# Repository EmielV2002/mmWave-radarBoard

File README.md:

# mmWave-radarBoard
 
# This is project is still work-in-progress!

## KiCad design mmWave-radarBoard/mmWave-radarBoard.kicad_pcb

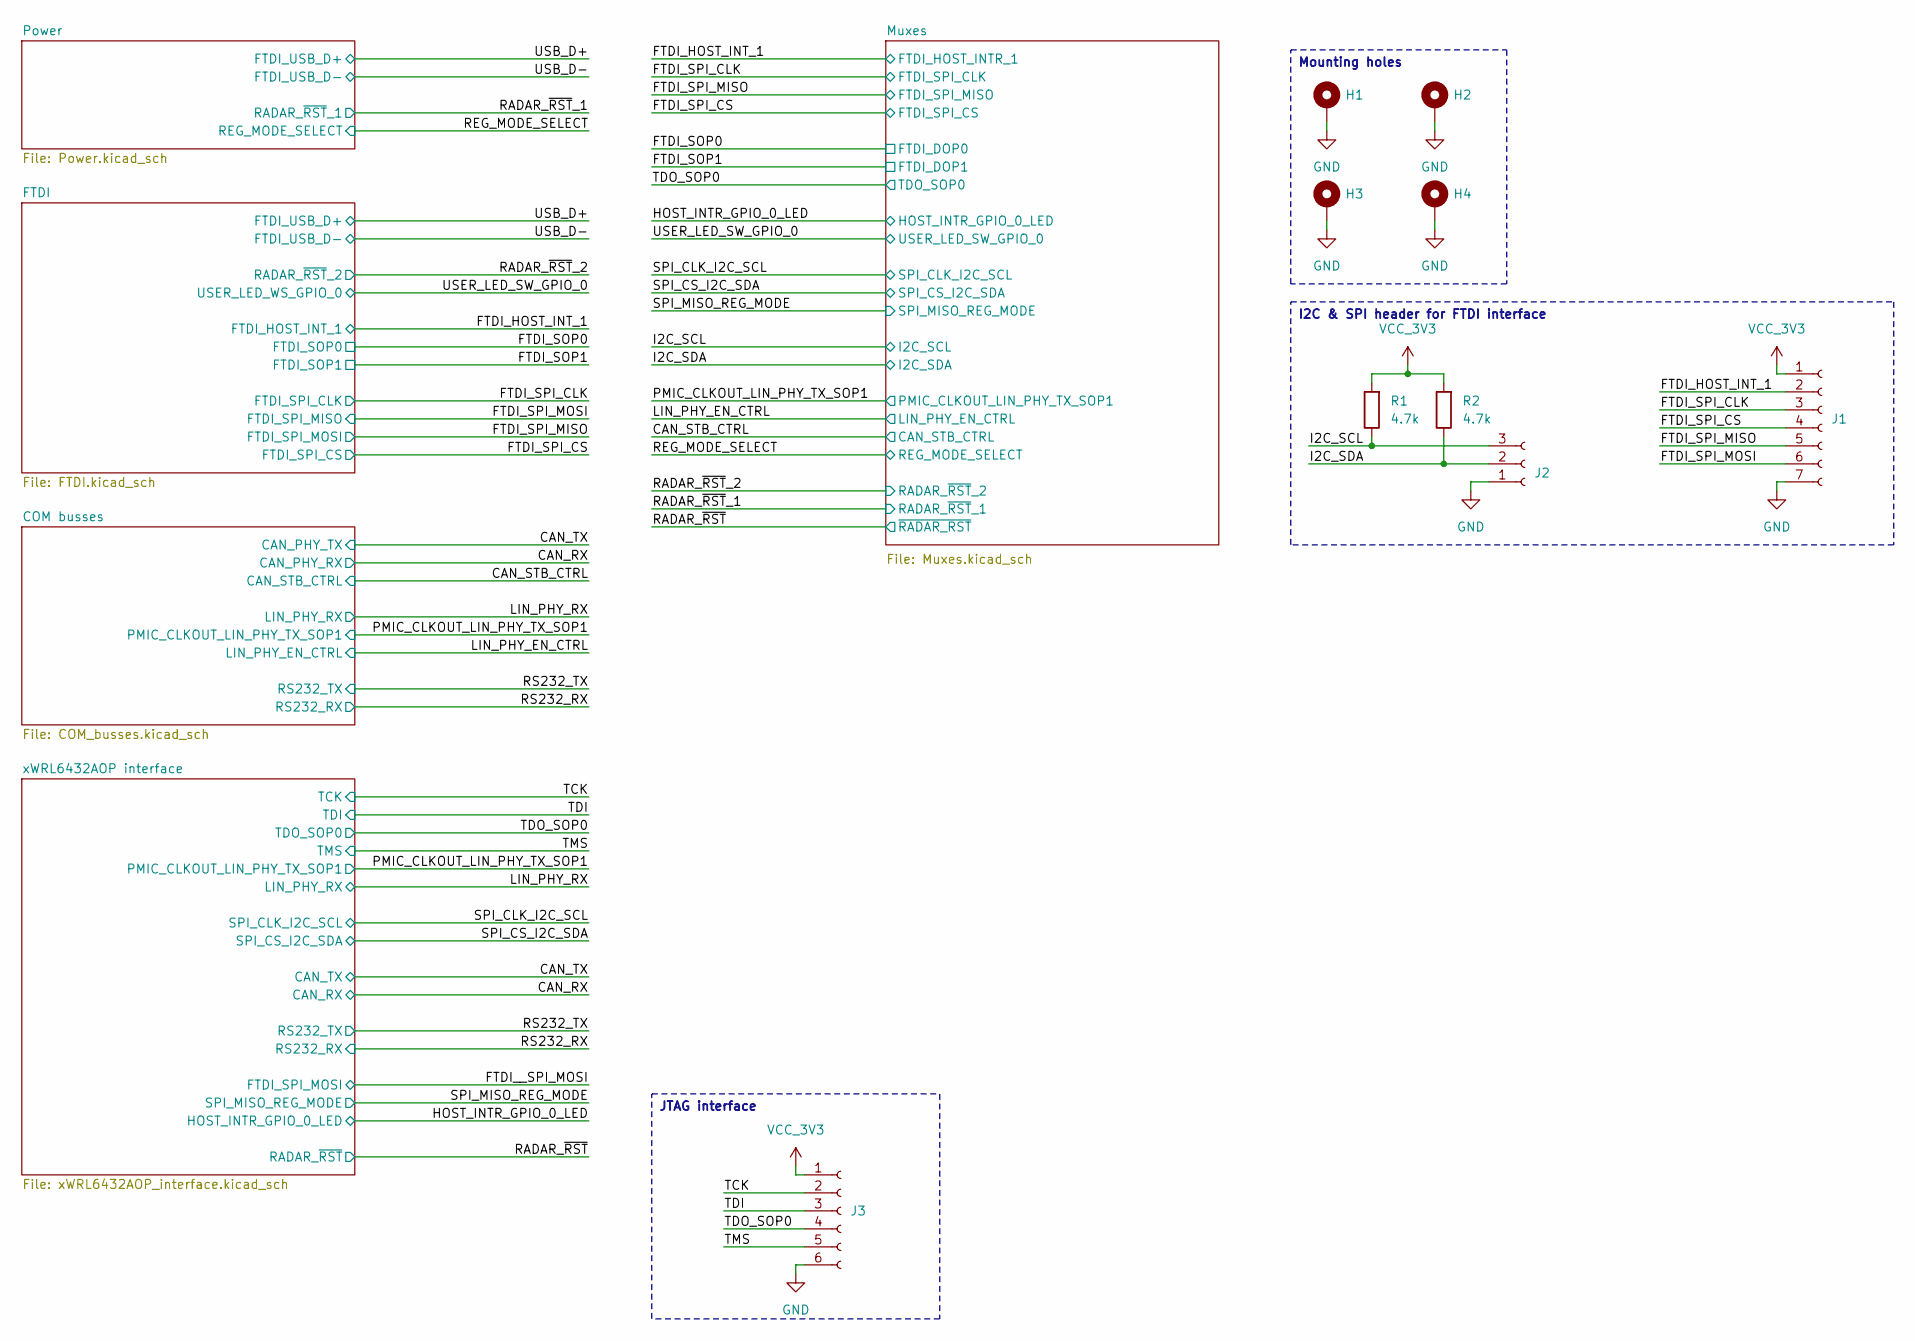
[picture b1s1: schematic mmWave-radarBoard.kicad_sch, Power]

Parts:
H1, H2, H3, H4: MountingHole; MountingHole_2.7mm_M2.5_DIN965_Pad
J1: Conn_01x07_Socket; JST_ZH_B7B-ZR_1x07_P1.50mm_Vertical
J2: Conn_01x03_Socket; JST_ZE_B03B-ZESK-D_1x03_P1.50mm_Vertical
J3: Conn_01x06_Socket; JST_ZH_B6B-ZR_1x06_P1.50mm_Vertical
R1, R2: 4.7k; R_0402_1005Metric

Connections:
/FTDI_HOST_INT_1: J1.2; also elsewhere on the board
/FTDI_SPI_CLK: J1.3; also elsewhere on the board
/FTDI_SPI_CS: J1.4; also elsewhere on the board
/FTDI_SPI_MISO: J1.5; also elsewhere on the board
/FTDI_SPI_MOSI: J1.6; also elsewhere on the board
/I2C_SCL: J2.3, R1.1; also elsewhere on the board
/I2C_SDA: J2.2, R2.1; also elsewhere on the board
/TCK: J3.2; also elsewhere on the board
/TDI: J3.3; also elsewhere on the board
/TDO_SOP0: J3.4; also elsewhere on the board
/TMS: J3.5; also elsewhere on the board
GND: H1.1, H2.1, H3.1, H4.1, J1.7, J2.1, J3.6; also elsewhere on the board
VCC_3V3: J1.1, J3.1, R1.2, R2.2; also elsewhere on the board

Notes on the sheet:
Mounting holes
I2C & SPI header for FTDI interface
JTAG interface

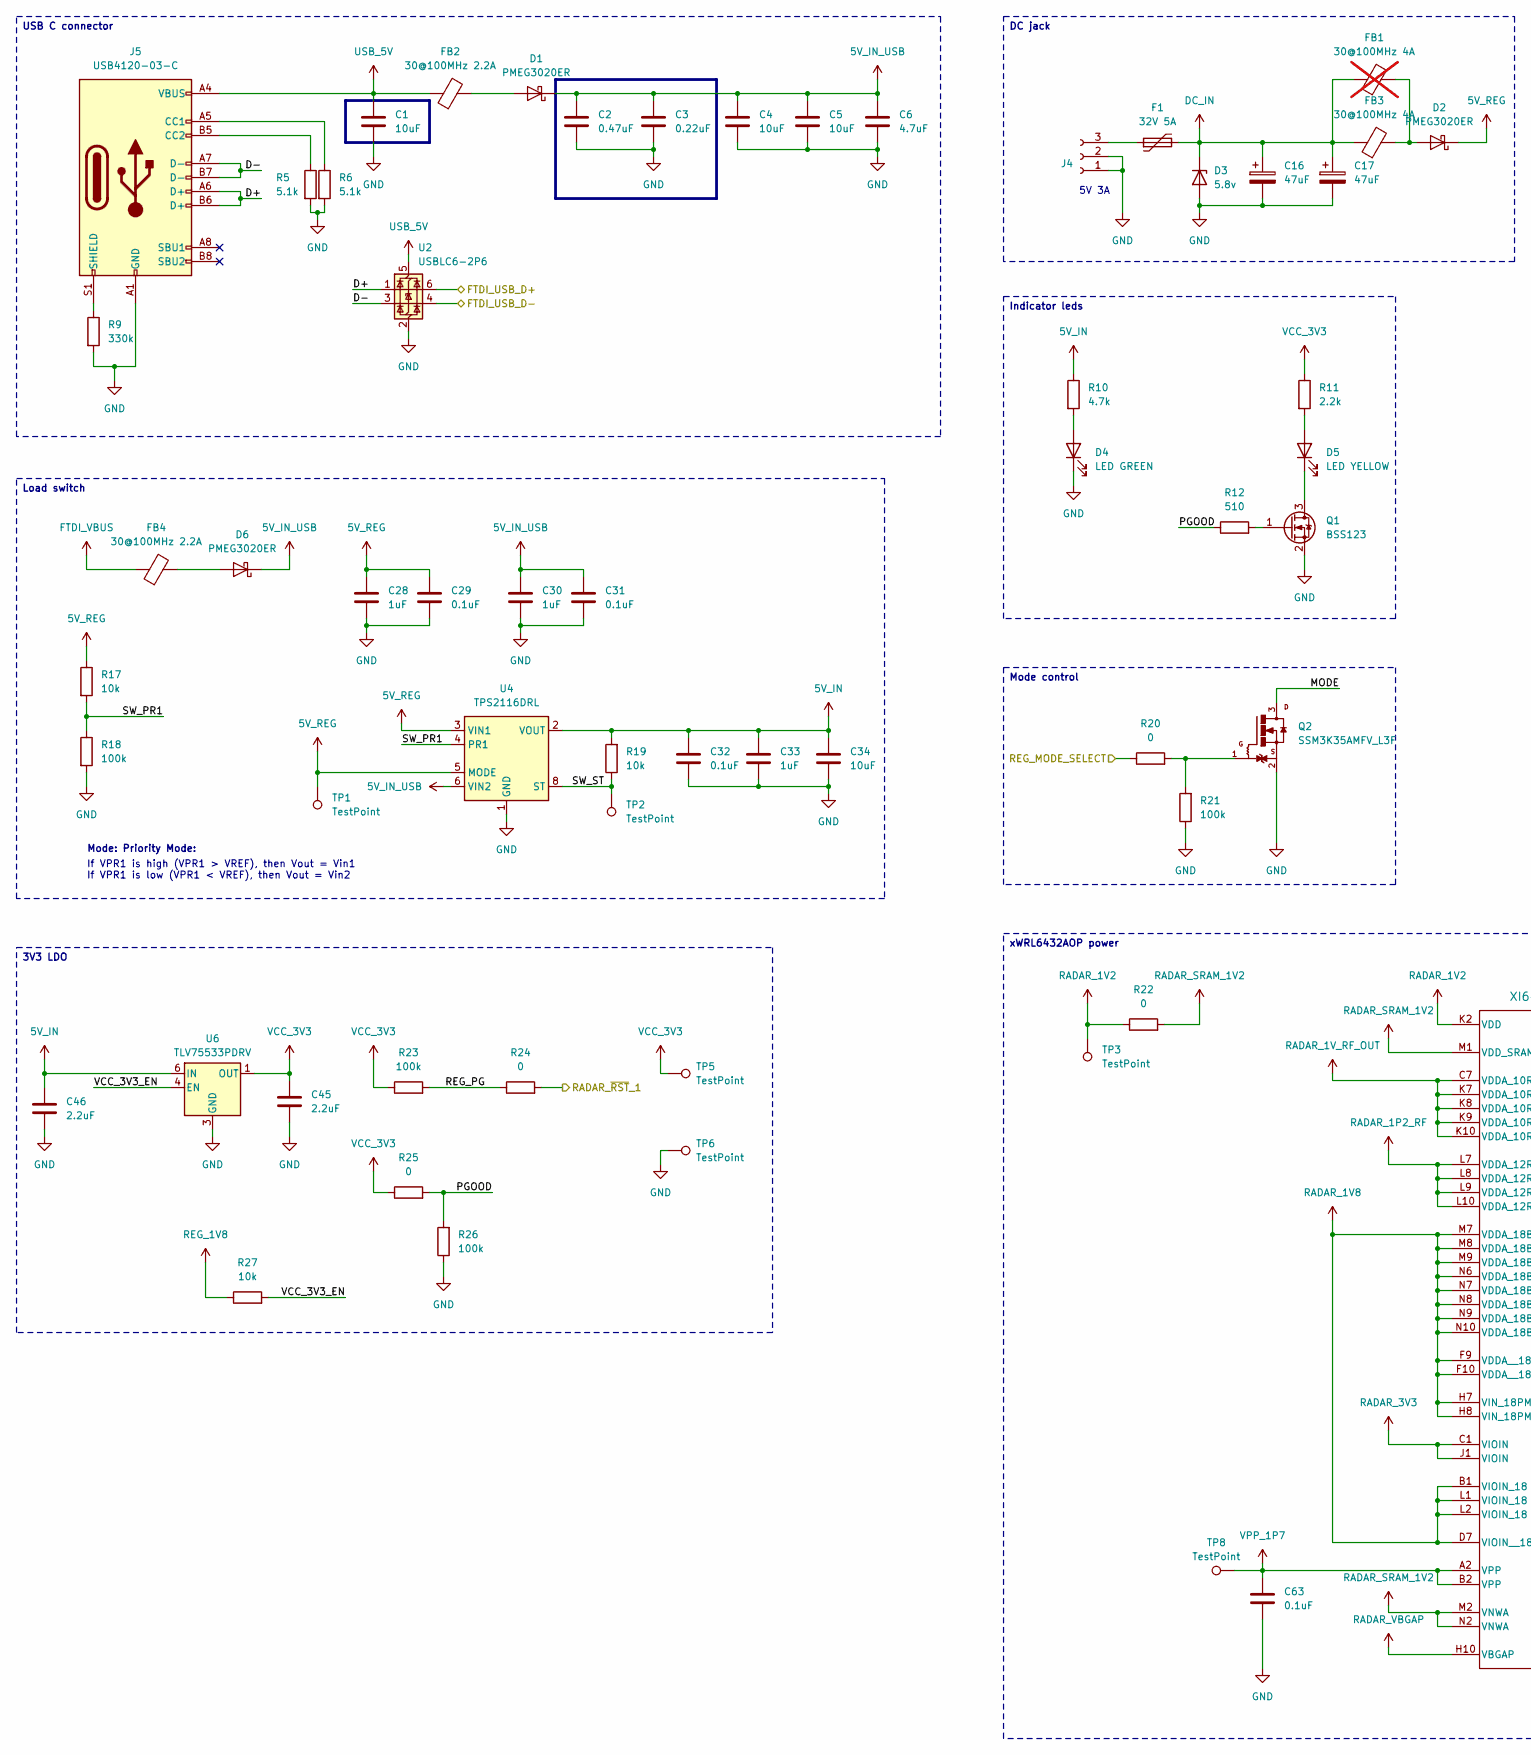
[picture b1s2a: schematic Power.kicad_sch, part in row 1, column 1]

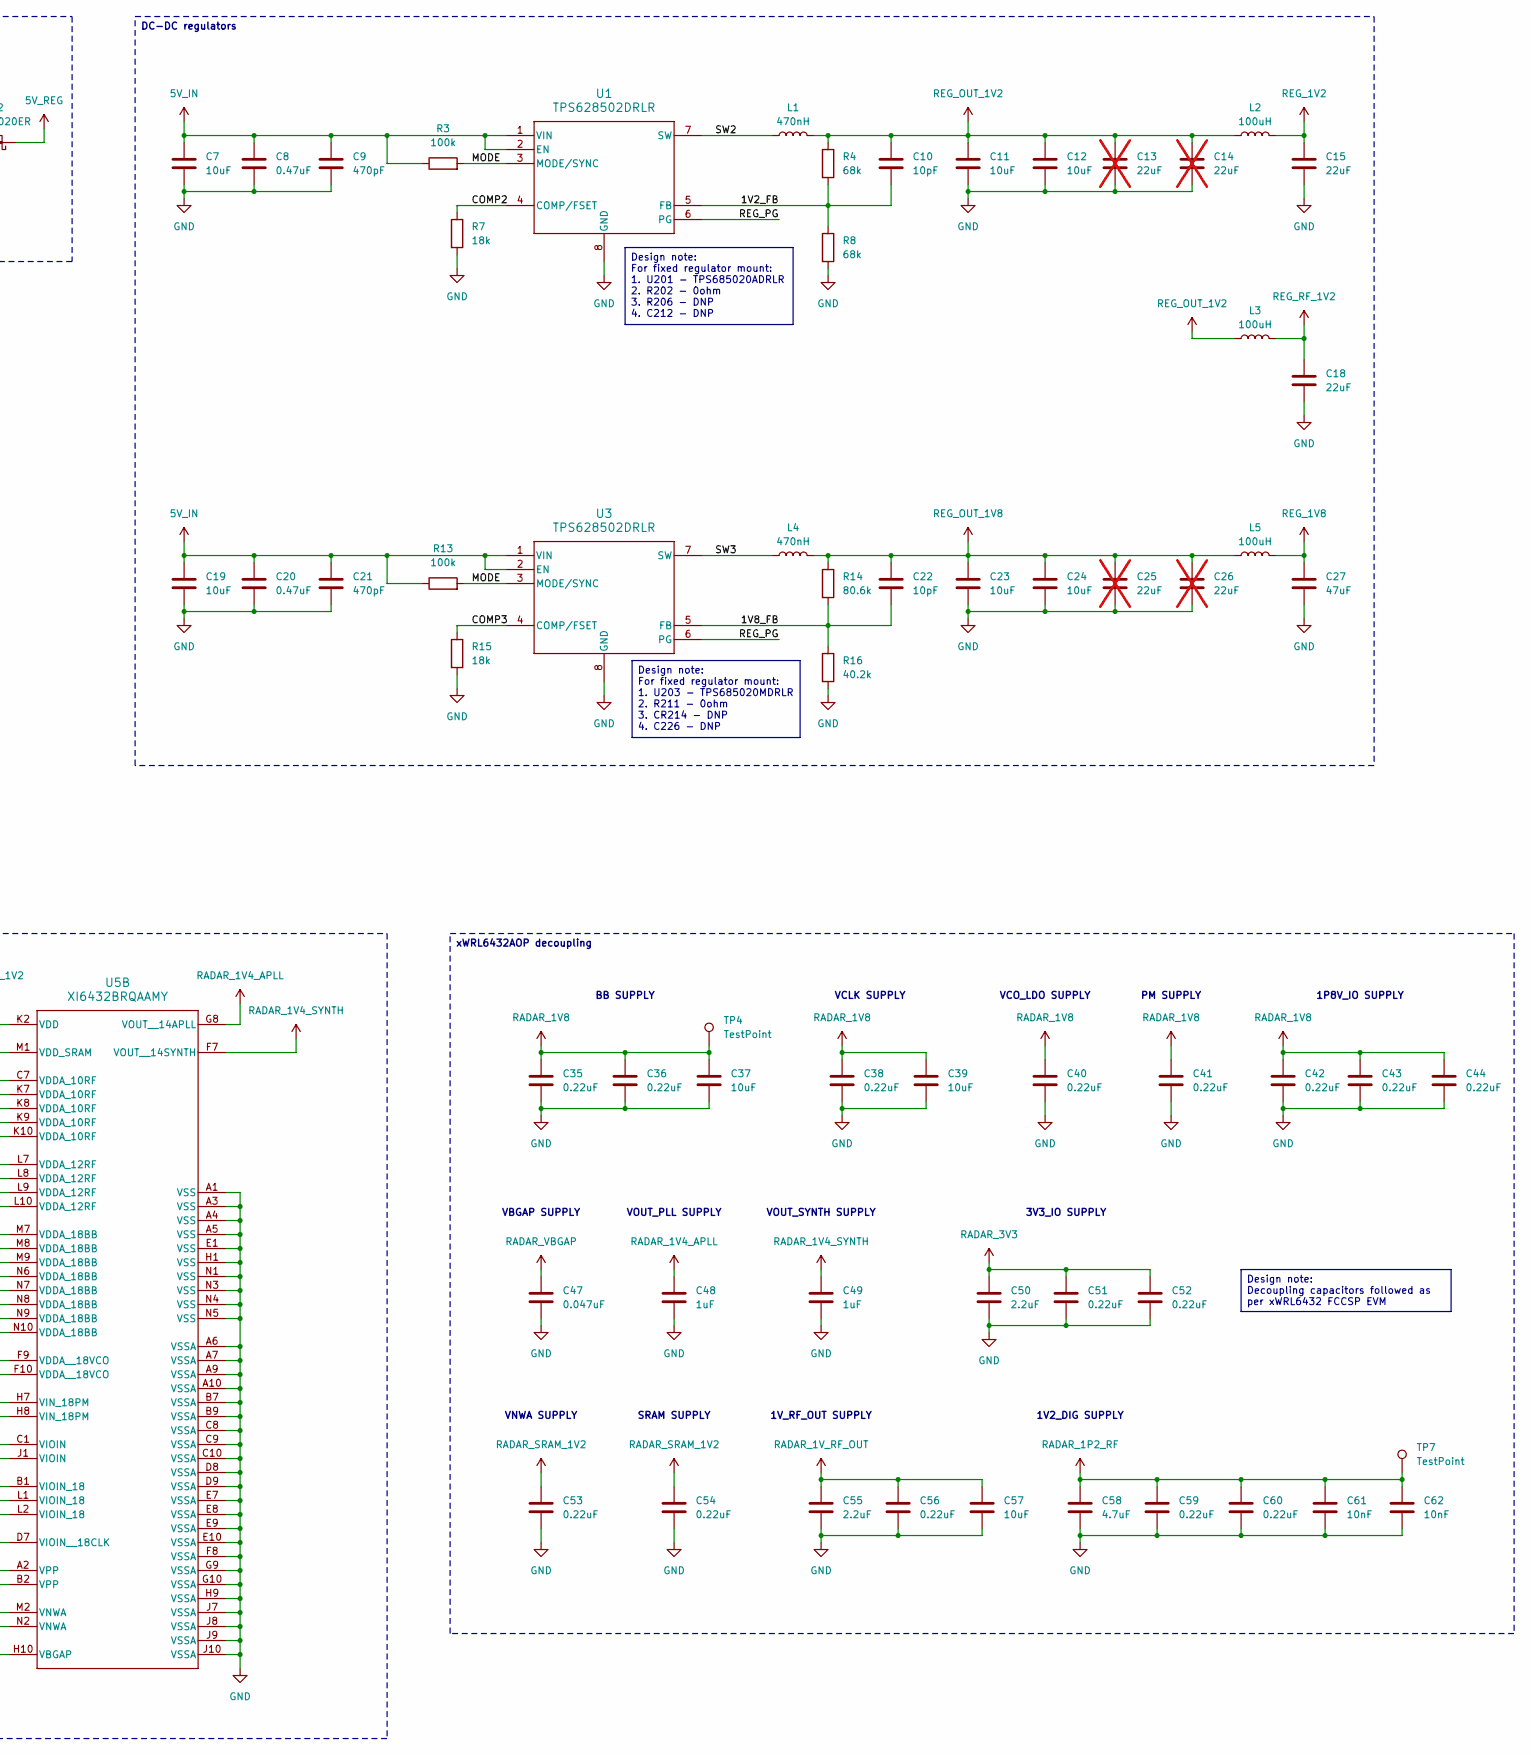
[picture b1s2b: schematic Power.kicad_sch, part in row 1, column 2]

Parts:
C1, C4, C5: 10uF; C_0805_2012Metric
C2: 0.47uF; C_0805_2012Metric
C3: 0.22uF; C_0805_2012Metric
C6: 4.7uF; C_0805_2012Metric
C7, C11, C12, C19, C23, C24, C34: 10uF; C_0603_1608Metric
C8, C20: 0.47uF; C_0603_1608Metric
C9, C21: 470pF; C_0603_1608Metric
C10, C22: 10pF; C_0402_1005Metric
C13, C14, C25, C26: 22uF; C_0603_1608Metric; not fitted
C15, C18: 22uF; C_0603_1608Metric
C16, C17: 47uF; CP_Elec_3x5.3
C27: 47uF; C_0603_1608Metric
C28, C30, C33: 1uF; C_0603_1608Metric
C29, C31, C32: 0.1uF; C_0603_1608Metric
C35, C36, C38, C40, C41, C42, C43, C44, C51, C52, C53, C54, C56, C59, C60: 0.22uF; C_0402_1005Metric
C37, C39, C57: 10uF; C_0402_1005Metric
C45, C46: 2.2uF; C_0603_1608Metric
C47: 0.047uF; C_0402_1005Metric
C48, C49: 1uF; C_0402_1005Metric
C50, C55: 2.2uF; C_0402_1005Metric
C58: 4.7uF; C_0402_1005Metric
C61, C62: 10nF; C_0402_1005Metric
C63: 0.1uF; C_0402_1005Metric
D1, D2, D6: PMEG3020ER; Nexperia_CFP3_SOD-123W
D3: 5.8v; D_SOD-123F
D4: LED GREEN; LED_0603_1608Metric
D5: LED YELLOW; LED_0603_1608Metric
F1: 32V 5A; Fuse_1812_4532Metric_Pad1.30x3.40mm_HandSolder
FB1: 30@100MHz 4A; L_0805_2012Metric; not fitted
FB2, FB4: 30@100MHz 2.2A; L_0805_2012Metric
FB3: 30@100MHz 4A; L_0805_2012Metric
J4: Conn_01x03_Socket; JST_ZE_B03B-ZESK-D_1x03_P1.50mm_Vertical
J5: USB4120-03-C; GCT_USB4120-03-C; PARTREV A
L1, L4: 470nH; L_0805_2012Metric
L2, L3, L5: 100uH; L_0805_2012Metric
Q1: BSS123; SOT-23
Q2: SSM3K35AMFV_L3F; VESM_TOS-M; MANUFACTURER_PART_NUMBER SSM3K35AMFV,L3F
R3, R13, R18, R21, R23, R26: 100k; R_0402_1005Metric
R4, R8: 68k; R_0402_1005Metric
R5, R6: 5.1k; R_0402_1005Metric
R7, R15: 18k; R_0402_1005Metric
R9: 330k; R_1206_3216Metric
R10: 4.7k; R_0603_1608Metric
R11: 2.2k; R_0603_1608Metric
R12: 510; R_0603_1608Metric
R14: 80.6k; R_0402_1005Metric
R16: 40.2k; R_0402_1005Metric
R17, R19, R27: 10k; R_0402_1005Metric
R20, R22, R24, R25: 0; R_0402_1005Metric
TP1, TP2, TP3, TP4, TP5, TP6, TP7, TP8: TestPoint; TestPoint_Pad_D1.0mm
U1, U3: TPS628502DRLR; SOT-5X3-8_DRL_TEX
U2: USBLC6-2P6; SOT-666
U4: TPS2116DRL; SOT-583-8
U5: XI6432BRQAAMY; FCCSP101_AMY_TEX
U6: TLV75533PDRV; WSON-6-1EP_2x2mm_P0.65mm_EP1x1.6mm

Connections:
5V_IN: C7.1, C8.1, C9.1, C19.1, C20.1, C21.1, C32.1, C33.1, C34.1, C46.1, R3.1, R10.1, R13.1, R19.2, U1.1 (VIN), U1.2 (EN), U3.1 (VIN), U3.2 (EN), U4.2 (VOUT), U4.7 (VOUT), U6.6 (IN); also elsewhere on the board
5V_IN_USB: C2.1, C3.1, C4.1, C5.1, C6.1, C30.1, C31.1, D1.1 (K), D6.1 (K), U4.6 (VIN2)
5V_REG: C28.1, C29.1, D2.1 (K), R17.1, TP1.1, U4.3 (VIN1), U4.5 (MODE)
/Power/1V2_FB: C10.2, R4.2, R8.1, U1.5 (FB)
/Power/1V8_FB: C22.2, R14.2, R16.1, U3.5 (FB)
/Power/COMP2: R7.1, U1.4 (COMP/FSET)
/Power/COMP3: R15.1, U3.4 (COMP/FSET)
/Power/D+: J5.A6 (D+), J5.B6 (D+), U2.1 (I/O1)
/Power/D-: J5.A7 (D-), J5.B7 (D-), U2.3 (I/O2)
/Power/MODE: Q2.3, R3.2, R13.2, U1.3 (MODE/SYNC), U3.3 (MODE/SYNC)
/Power/PGOOD: R12.1, R25.2, R26.2
/Power/REG_PG: R23.2, R24.1, U1.6 (PG), U3.6 (PG)
/Power/SW2: L1.1, U1.7 (SW)
/Power/SW3: L4.1, U3.7 (SW)
/Power/SW_PR1: R17.2, R18.1, U4.4 (PR1)
/Power/SW_ST: R19.1, TP2.1, U4.8 (ST)
/Power/VCC_3V3_EN: R27.2, U6.4 (EN)
/RADAR_~RST_1: R24.2; also elsewhere on the board
/REG_MODE_SELECT: R20.1; also elsewhere on the board
/USB_D+: U2.6 (I/O1); also elsewhere on the board
/USB_D-: U2.4 (I/O2); also elsewhere on the board
DC_IN: C16.1, C17.1, D3.1 (K), F1.2, FB1.1, FB3.1
FTDI_VBUS: FB4.1
GND: C1.2, C2.2, C3.2, C4.2, C5.2, C6.2, C7.2, C8.2, C9.2, C11.2, C12.2, C13.2, C14.2, C15.2, C16.2, C17.2, C18.2, C19.2, C20.2, C21.2, C23.2, C24.2, C25.2, C26.2, C27.2, C28.2, C29.2, C30.2, C31.2, C32.2, C33.2, C34.2, C35.2, C36.2, C37.2, C38.2, C39.2, C40.2, C41.2, C42.2, C43.2, C44.2, C45.2, C46.2, C47.2, C48.2, C49.2, C50.2, C51.2, C52.2, C53.2, C54.2, C55.2, C56.2, C57.2, C58.2, C59.2, C60.2, C61.2, C62.2, C63.2, D3.2 (A), D4.1 (K), J4.1, J4.2, J5.A1 (GND), J5.A12 (GND), J5.B1 (GND), J5.B12 (GND), Q1.2 (S), Q2.2, R5.2, R6.2, R7.2, R8.2, R9.2, R15.2, R16.2, R18.2, R21.1, R26.1, TP6.1, U1.8 (GND), U2.2 (GND), U3.8 (GND), U4.1 (GND), U5.A1 (VSS), U5.A3 (VSS), U5.A4 (VSS), U5.A5 (VSS), U5.A6 (VSSA), U5.A7 (VSSA), U5.A9 (VSSA), U5.A10 (VSSA), U5.B7 (VSSA), U5.B9 (VSSA), U5.C8 (VSSA), U5.C9 (VSSA), U5.C10 (VSSA), U5.D8 (VSSA), U5.D9 (VSSA), U5.E1 (VSS), U5.E7 (VSSA), U5.E8 (VSSA), U5.E9 (VSSA), U5.E10 (VSSA), U5.F8 (VSSA), U5.G9 (VSSA), U5.G10 (VSSA), U5.H1 (VSS), U5.H9 (VSSA), U5.J7 (VSSA), U5.J8 (VSSA), U5.J9 (VSSA), U5.J10 (VSSA), U5.N1 (VSS), U5.N3 (VSS), U5.N4 (VSS), U5.N5 (VSS), U6.3 (GND), U6.7 (GND); also elsewhere on the board
unnamed: D1.2 (A), FB2.2
unnamed: D2.2 (A), FB1.2, FB3.2
unnamed: D4.2 (A), R10.2
unnamed: D5.2 (A), R11.2
unnamed: D5.1 (K), Q1.3 (D)
unnamed: D6.2 (A), FB4.2
unnamed: F1.1, J4.3
unnamed: J5.A5 (CC1), R6.1
unnamed: J5.B5 (CC2), R5.1
unnamed: J5.S1 (SHIELD), J5.S2 (SHIELD), J5.S3 (SHIELD), J5.S4 (SHIELD), R9.1
unnamed: Q1.1 (G), R12.2
unnamed: Q2.1, R20.2, R21.2
RADAR_1P2_RF: C58.1, C59.1, C60.1, C61.1, C62.1, TP7.1, U5.L7 (VDDA_12RF), U5.L8 (VDDA_12RF), U5.L9 (VDDA_12RF), U5.L10 (VDDA_12RF)
RADAR_1V2: R22.1, TP3.1, U5.K2 (VDD); also elsewhere on the board
RADAR_1V4_APLL: C48.1, U5.G8 (VOUT__14APLL)
RADAR_1V4_SYNTH: C49.1, U5.F7 (VOUT__14SYNTH)
RADAR_1V8: C35.1, C36.1, C37.1, C38.1, C39.1, C40.1, C41.1, C42.1, C43.1, C44.1, TP4.1, U5.B1 (VIOIN_18), U5.D7 (VIOIN__18CLK), U5.F9 (VDDA__18VCO), U5.F10 (VDDA__18VCO), U5.H7 (VIN_18PM), U5.H8 (VIN_18PM), U5.L1 (VIOIN_18), U5.L2 (VIOIN_18), U5.M7 (VDDA_18BB), U5.M8 (VDDA_18BB), U5.M9 (VDDA_18BB), U5.N6 (VDDA_18BB), U5.N7 (VDDA_18BB), U5.N8 (VDDA_18BB), U5.N9 (VDDA_18BB), U5.N10 (VDDA_18BB)
RADAR_1V_RF_OUT: C55.1, C56.1, C57.1, U5.C7 (VDDA_10RF), U5.K7 (VDDA_10RF), U5.K8 (VDDA_10RF), U5.K9 (VDDA_10RF), U5.K10 (VDDA_10RF)
RADAR_3V3: C50.1, C51.1, C52.1, U5.C1 (VIOIN), U5.J1 (VIOIN); also elsewhere on the board
RADAR_SRAM_1V2: C53.1, C54.1, R22.2, U5.M1 (VDD_SRAM), U5.M2 (VNWA), U5.N2 (VNWA)
RADAR_VBGAP: C47.1, U5.H10 (VBGAP)
REG_1V2: C15.1, L2.2
REG_1V8: C27.1, L5.2, R27.1
REG_OUT_1V2: C10.1, C11.1, C12.1, C13.1, C14.1, L1.2, L2.1, L3.1, R4.1
REG_OUT_1V8: C22.1, C23.1, C24.1, C25.1, C26.1, L4.2, L5.1, R14.1
REG_RF_1V2: C18.1, L3.2
USB_5V: C1.1, FB2.1, J5.A4 (VBUS), J5.A9 (VBUS), J5.B4 (VBUS), J5.B9 (VBUS), U2.5 (VBUS)
VCC_3V3: C45.1, R11.1, R23.1, R25.1, TP5.1, U6.1 (OUT); also elsewhere on the board
VPP_1P7: C63.1, TP8.1, U5.A2 (VPP), U5.B2 (VPP)

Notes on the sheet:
5V 3A
1V2_DIG SUPPLY
VCO_LDO SUPPLY
VCLK SUPPLY
VOUT_SYNTH SUPPLY
Mode: Priority Mode:
VNWA SUPPLY
1V_RF_OUT SUPPLY
1P8V_IO SUPPLY
If VPR1 is high (VPR1 > VREF), then Vout = Vin1 If VPR1 is low (VPR1 < VREF), then Vout = Vin2
BB SUPPLY
3V3_IO SUPPLY
PM SUPPLY
VBGAP SUPPLY
SRAM SUPPLY
VOUT_PLL SUPPLY
USB C connector
xWRL6432AOP decoupling
xWRL6432AOP power
Design note: Decoupling capacitors followed as per xWRL6432 FCCSP EVM
DC jack
Design note: For fixed regulator mount: 1. U203 - TPS685020MDRLR 2. R211 - 0ohm 3. CR214 - DNP 4. C226 - DNP
Load switch
Mode control
DC-DC regulators
Indicator leds
3V3 LDO
Design note: For fixed regulator mount: 1. U201 - TPS685020ADRLR 2. R202 - 0ohm 3. R206 - DNP 4. C212 - DNP

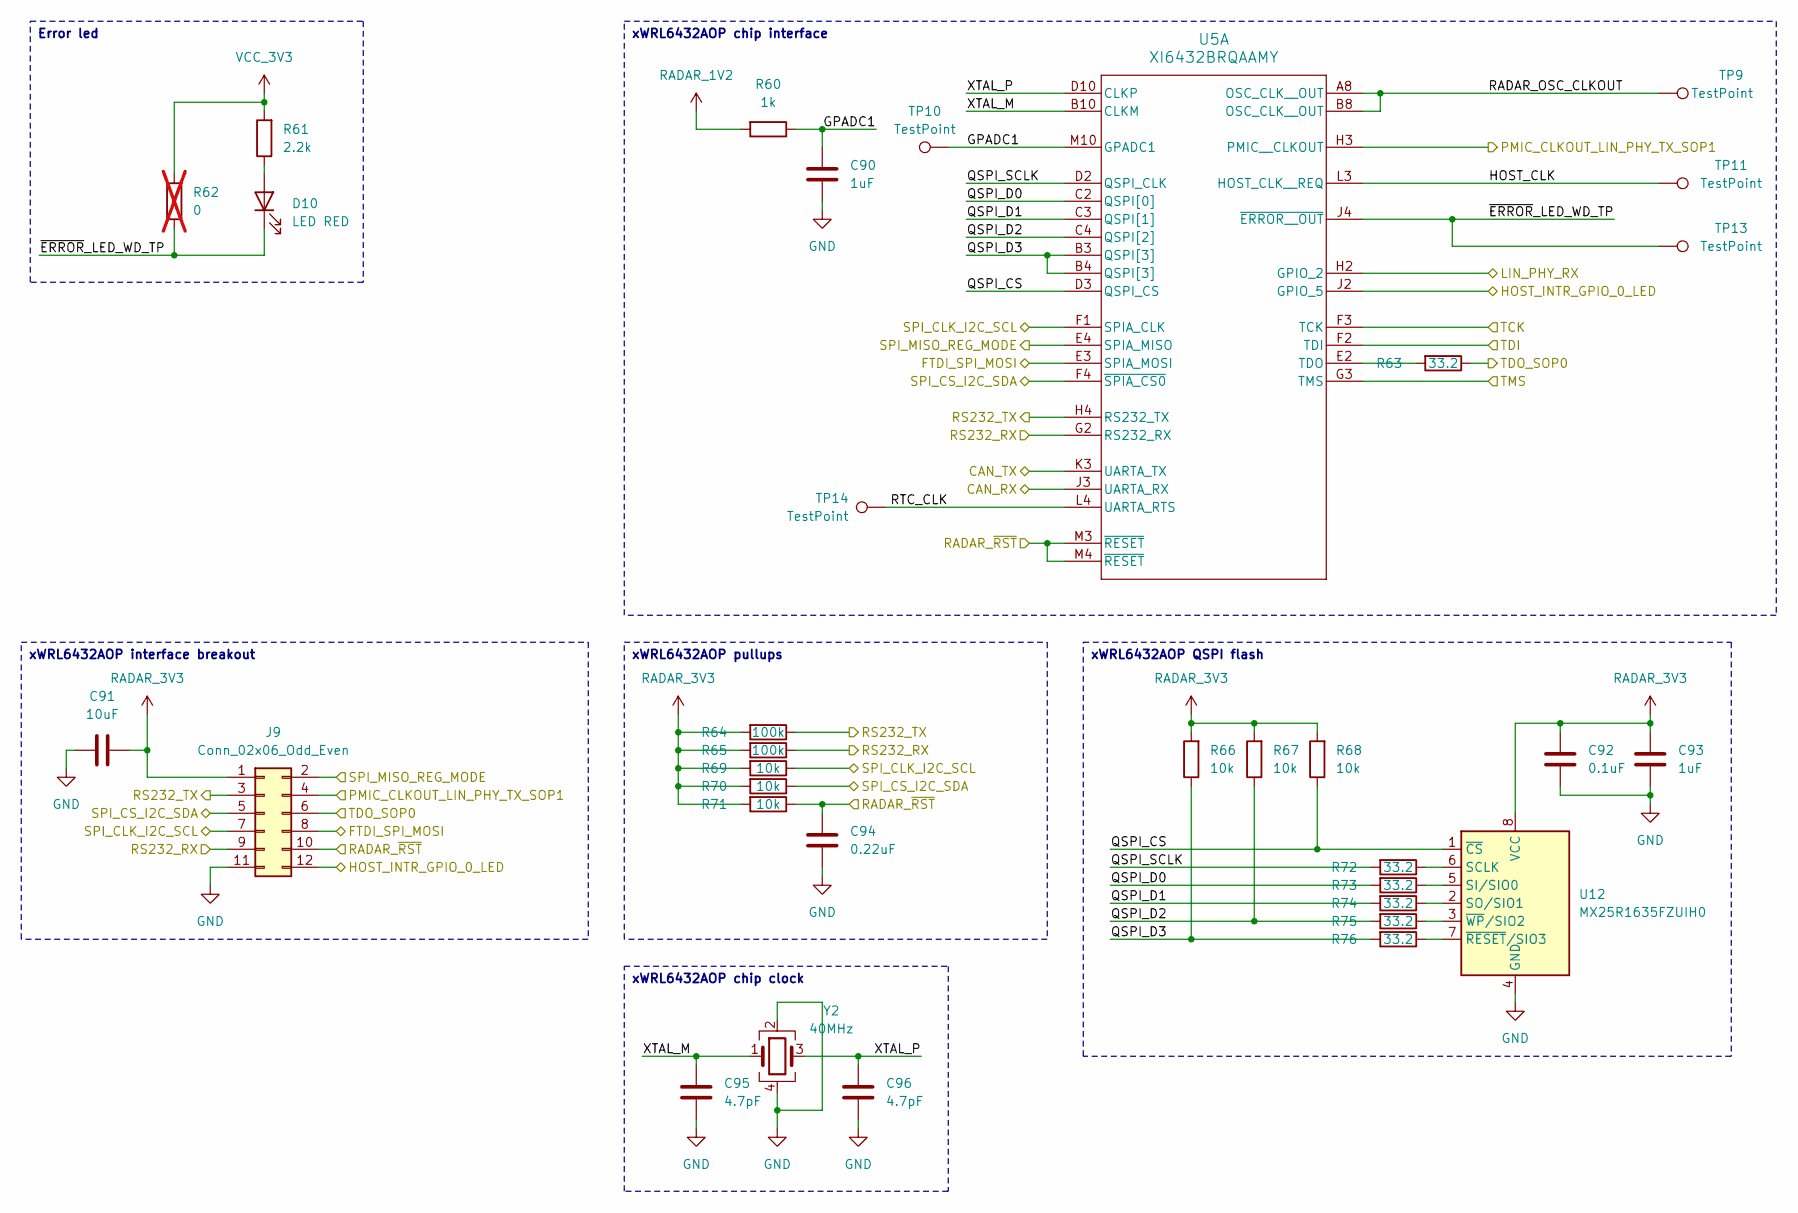
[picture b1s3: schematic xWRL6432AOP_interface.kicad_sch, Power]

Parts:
C90: 1uF; C_0402_1005Metric
C91: 10uF; C_0603_1608Metric
C92: 0.1uF; C_0402_1005Metric
C93: 1uF; C_0603_1608Metric
C94: 0.22uF; C_0402_1005Metric
C95, C96: 4.7pF; C_0402_1005Metric
D10: LED RED; LED_0603_1608Metric
J9: Conn_02x06_Odd_Even; JST_PUD_B12B-PUDSS_2x06_P2.00mm_Vertical
R60: 1k; R_0402_1005Metric
R61: 2.2k; R_0603_1608Metric
R62: 0; R_0603_1608Metric; not fitted
R63, R72, R73, R74, R75, R76: 33.2; R_0402_1005Metric
R64, R65: 100k; R_0402_1005Metric
R66, R67, R68, R69, R70, R71: 10k; R_0402_1005Metric
TP9, TP10, TP11, TP13, TP14: TestPoint; TestPoint_Pad_D1.0mm
U5: XI6432BRQAAMY; FCCSP101_AMY_TEX
U12: MX25R1635FZUIH0; PSON50P200X300X60-9N
Y2: 40MHz; Crystal_SMD_2016-4Pin_2.0x1.6mm

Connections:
/CAN_RX: U5.J3 (UARTA_RX); also elsewhere on the board
/CAN_TX: U5.K3 (UARTA_TX); also elsewhere on the board
/FTDI__SPI_MOSI: J9.8, U5.E3 (SPIA_MOSI)
/HOST_INTR_GPIO_0_LED: J9.12, U5.J2 (GPIO_5); also elsewhere on the board
/LIN_PHY_RX: U5.H2 (GPIO_2); also elsewhere on the board
/PMIC_CLKOUT_LIN_PHY_TX_SOP1: J9.4, U5.H3 (PMIC__CLKOUT); also elsewhere on the board
/RADAR_~RST: C94.1, J9.10, R71.1, U5.M3 (~RESET), U5.M4 (~RESET); also elsewhere on the board
/RS232_RX: J9.9, R65.1, U5.G2 (RS232_RX); also elsewhere on the board
/RS232_TX: J9.3, R64.1, U5.H4 (RS232_TX); also elsewhere on the board
/SPI_CLK_I2C_SCL: J9.7, R69.1, U5.F1 (SPIA_CLK); also elsewhere on the board
/SPI_CS_I2C_SDA: J9.5, R70.1, U5.F4 (~SPIA_CS0); also elsewhere on the board
/SPI_MISO_REG_MODE: J9.2, U5.E4 (SPIA_MISO); also elsewhere on the board
/TCK: U5.F3 (TCK); also elsewhere on the board
/TDI: U5.F2 (TDI); also elsewhere on the board
/TDO_SOP0: J9.6, R63.1; also elsewhere on the board
/TMS: U5.G3 (TMS); also elsewhere on the board
/xWRL6432AOP interface/GPADC1: C90.1, R60.1, TP10.1, U5.M10 (GPADC1)
/xWRL6432AOP interface/HOST_CLK: TP11.1, U5.L3 (HOST_CLK__REQ)
/xWRL6432AOP interface/QSPI_CS: R68.1, U5.D3 (QSPI_CS), U12.1 (~CS)
/xWRL6432AOP interface/QSPI_D0: R73.2, U5.C2 (QSPI[0])
/xWRL6432AOP interface/QSPI_D1: R74.2, U5.C3 (QSPI[1])
/xWRL6432AOP interface/QSPI_D2: R67.1, R75.2, U5.C4 (QSPI[2])
/xWRL6432AOP interface/QSPI_D3: R66.1, R76.2, U5.B3 (QSPI[3]), U5.B4 (QSPI[3])
/xWRL6432AOP interface/QSPI_SCLK: R72.2, U5.D2 (QSPI_CLK)
/xWRL6432AOP interface/RADAR_OSC_CLKOUT: TP9.1, U5.A8 (OSC_CLK__OUT), U5.B8 (OSC_CLK__OUT)
/xWRL6432AOP interface/RTC_CLK: TP14.1, U5.L4 (UARTA_RTS)
/xWRL6432AOP interface/XTAL_M: C95.1, U5.B10 (CLKM), Y2.1
/xWRL6432AOP interface/XTAL_P: C96.1, U5.D10 (CLKP), Y2.3
/xWRL6432AOP interface/~ERROR_LED_WD_TP: D10.1 (K), R62.1, TP13.1, U5.J4 (~ERROR__OUT)
GND: C90.2, C91.1, C92.2, C93.2, C94.2, C95.2, C96.2, J9.11, U12.4 (GND), U12.9 (GND), Y2.2, Y2.4; also elsewhere on the board
unnamed: D10.2 (A), R61.1
unnamed: R63.2, U5.E2 (TDO)
unnamed: R72.1, U12.6 (SCLK)
unnamed: R73.1, U12.5 (SI/SIO0)
unnamed: R74.1, U12.2 (SO/SIO1)
unnamed: R76.1, U12.7 (~RESET/SIO3)
unnamed: R75.1, U12.3 (~WP/SIO2)
RADAR_1V2: R60.2; also elsewhere on the board
RADAR_3V3: C91.2, C92.1, C93.1, J9.1, R64.2, R65.2, R66.2, R67.2, R68.2, R69.2, R70.2, R71.2, U12.8 (VCC); also elsewhere on the board
VCC_3V3: R61.2, R62.2; also elsewhere on the board

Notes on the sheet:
xWRL6432AOP QSPI flash
xWRL6432AOP chip clock
xWRL6432AOP pullups
Error led
xWRL6432AOP interface breakout
xWRL6432AOP chip interface

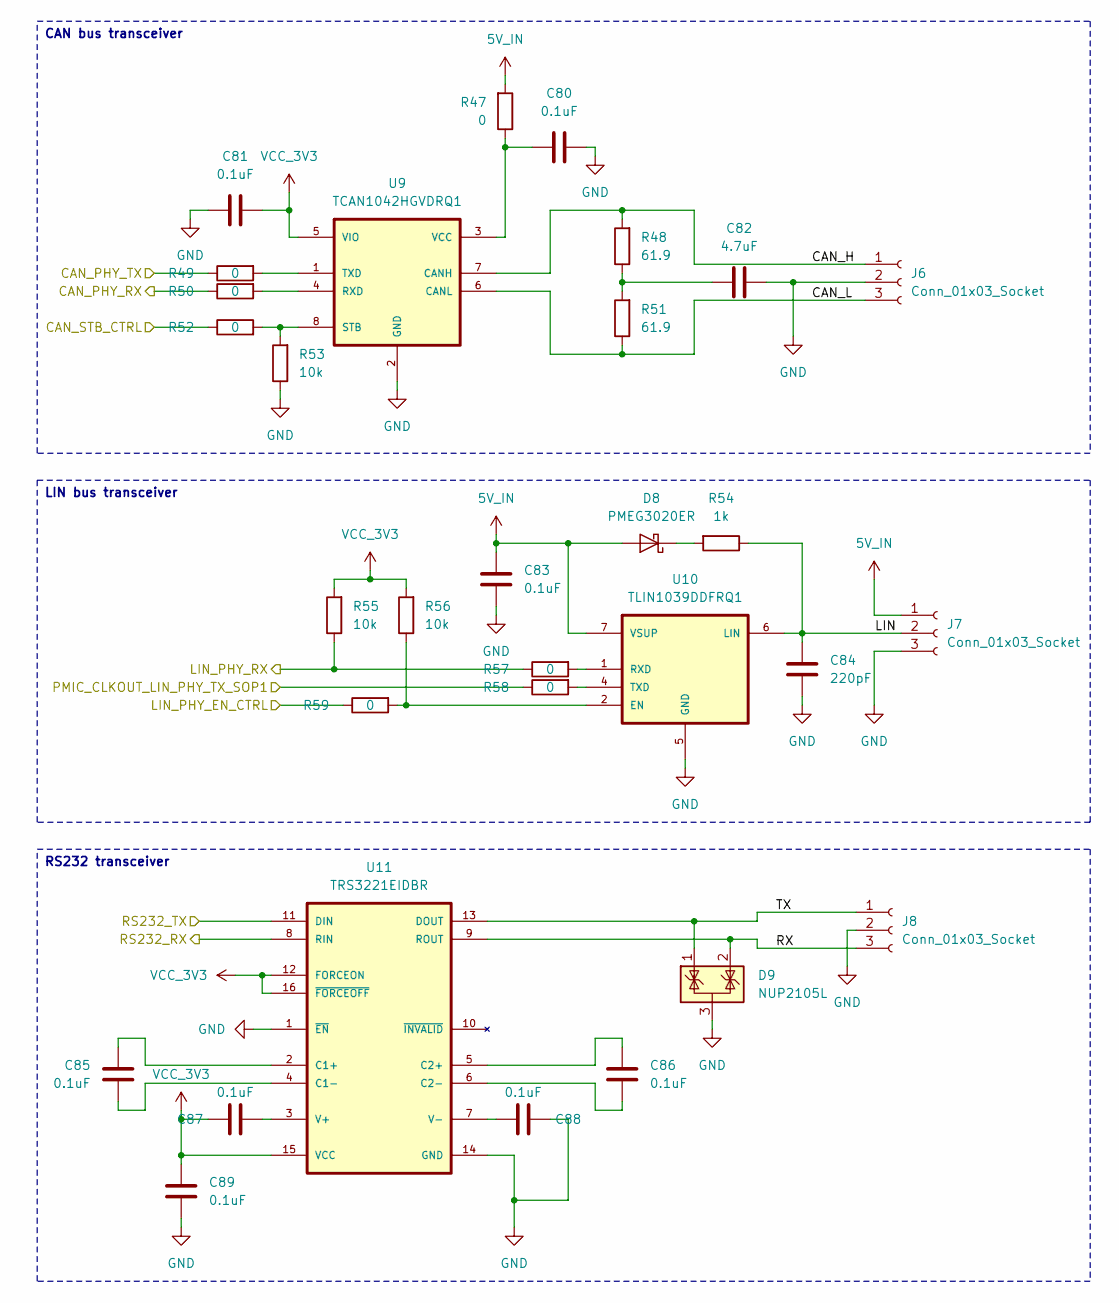
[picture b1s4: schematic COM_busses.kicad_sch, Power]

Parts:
C80, C81, C83, C85, C86, C87, C88, C89: 0.1uF; C_0603_1608Metric
C82: 4.7uF; C_0805_2012Metric
C84: 220pF; C_0805_2012Metric
D8: PMEG3020ER; Nexperia_CFP3_SOD-123W
D9: NUP2105L; SOT-23
J6, J7, J8: Conn_01x03_Socket; JST_ZE_B03B-ZESK-D_1x03_P1.50mm_Vertical
R47, R49, R50, R52, R57, R58, R59: 0; R_0402_1005Metric
R48, R51: 61.9; R_0402_1005Metric
R53, R55, R56: 10k; R_0402_1005Metric
R54: 1k; R_0805_2012Metric
U9: TCAN1042HGVDRQ1; SOIC127P599X175-8N
U10: TLIN1039DDFRQ1; SOT65P280X110-8N
U11: TRS3221EIDBR; SOP65P780X200-16N; MPN TRS3221EIDBR

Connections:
5V_IN: C83.2, D8.2 (A), J7.1, R47.2, U10.7 (VSUP); also elsewhere on the board
/CAN_RX: R50.1; also elsewhere on the board
/CAN_STB_CTRL: R52.1; also elsewhere on the board
/CAN_TX: R49.1; also elsewhere on the board
/COM busses/CAN_H: J6.1, R48.2, U9.7 (CANH)
/COM busses/CAN_L: J6.3, R51.1, U9.6 (CANL)
/COM busses/LIN: C84.2, J7.2, R54.1, U10.6 (LIN)
/COM busses/RX: D9.2 (K), J8.3, U11.9 (ROUT)
/COM busses/TX: D9.1 (K), J8.1, U11.13 (DOUT)
/LIN_PHY_EN_CTRL: R59.1; also elsewhere on the board
/LIN_PHY_RX: R55.1, R57.1; also elsewhere on the board
/PMIC_CLKOUT_LIN_PHY_TX_SOP1: R58.1; also elsewhere on the board
/RS232_RX: U11.8 (RIN); also elsewhere on the board
/RS232_TX: U11.11 (DIN); also elsewhere on the board
GND: C80.2, C81.1, C82.2, C83.1, C84.1, C88.1, C89.1, D9.3 (A), J6.2, J7.3, J8.2, R53.1, U9.2 (GND), U10.5 (GND), U11.1 (~EN), U11.14 (GND); also elsewhere on the board
unnamed: C82.1, R48.1, R51.2
unnamed: D8.1 (K), R54.2
unnamed: R50.2, U9.4 (RXD)
unnamed: R52.2, R53.2, U9.8 (STB)
unnamed: R49.2, U9.1 (TXD)
unnamed: C80.1, R47.1, U9.3 (VCC)
unnamed: R56.1, R59.2, U10.2 (EN)
unnamed: R57.2, U10.1 (RXD)
unnamed: R58.2, U10.4 (TXD)
unnamed: C85.1, U11.2 (C1+)
unnamed: C85.2, U11.4 (C1-)
unnamed: C86.1, U11.5 (C2+)
unnamed: C86.2, U11.6 (C2-)
unnamed: C87.1, U11.3 (V+)
unnamed: C88.2, U11.7 (V-)
VCC_3V3: C81.2, C87.2, C89.2, R55.2, R56.2, U9.5 (VIO), U11.12 (FORCEON), U11.15 (VCC), U11.16 (~FORCEOFF); also elsewhere on the board

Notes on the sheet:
LIN bus transceiver
RS232 transceiver
CAN bus transceiver

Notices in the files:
parts and their libraries:
COPYRIGHT: Copyright (C) 2024 Ultra Librarian. All rights reserved.
